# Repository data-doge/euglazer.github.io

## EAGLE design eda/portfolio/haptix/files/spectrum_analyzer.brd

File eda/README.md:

euglazer.github.io
==================

My EDA Phase 0 github pages site

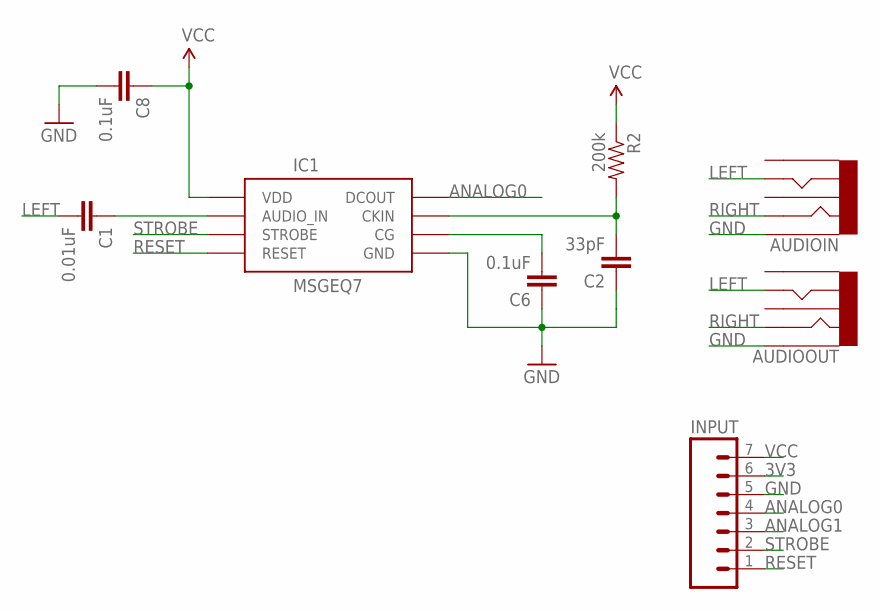
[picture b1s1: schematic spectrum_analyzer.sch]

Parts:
AUDIOIN: AUDIO-JACK2; AUDIO-JACK
AUDIOOUT: AUDIO-JACK2; AUDIO-JACK
C1: 0.01uF; 0603-CAP
C2: 33pF; 0603-CAP
C6, C8: 0.1uF; 0603-CAP
IC1: MSGEQ7DIL; DIL-08
INPUT: M07; 1X07
R2: 200k; 0603-RES

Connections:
3V3: INPUT.6
ANALOG0: IC1.3 (DCOUT), INPUT.4
ANALOG1: INPUT.3
CKIN: C2.2, IC1.8 (CKIN), R2.2
GND: AUDIOIN.1, AUDIOOUT.1, C2.1, C6.1, C8.2, IC1.2 (GND), INPUT.5
LEFT: AUDIOIN.5, AUDIOOUT.5, C1.2
unnamed: C1.1, IC1.5 (AUDIO_IN)
unnamed: C6.2, IC1.6 (CG)
RESET: IC1.7 (RESET), INPUT.1
RIGHT: AUDIOIN.2, AUDIOOUT.2
STROBE: IC1.4 (STROBE), INPUT.2
VCC: C8.1, IC1.1 (VDD), INPUT.7, R2.1

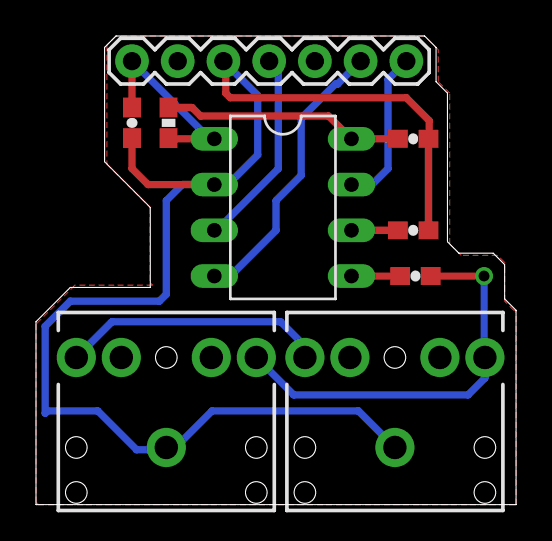
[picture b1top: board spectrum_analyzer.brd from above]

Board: 2 copper layers, 26.7 x 26.0 mm, 9 parts (0 on the bottom side), 10 nets.

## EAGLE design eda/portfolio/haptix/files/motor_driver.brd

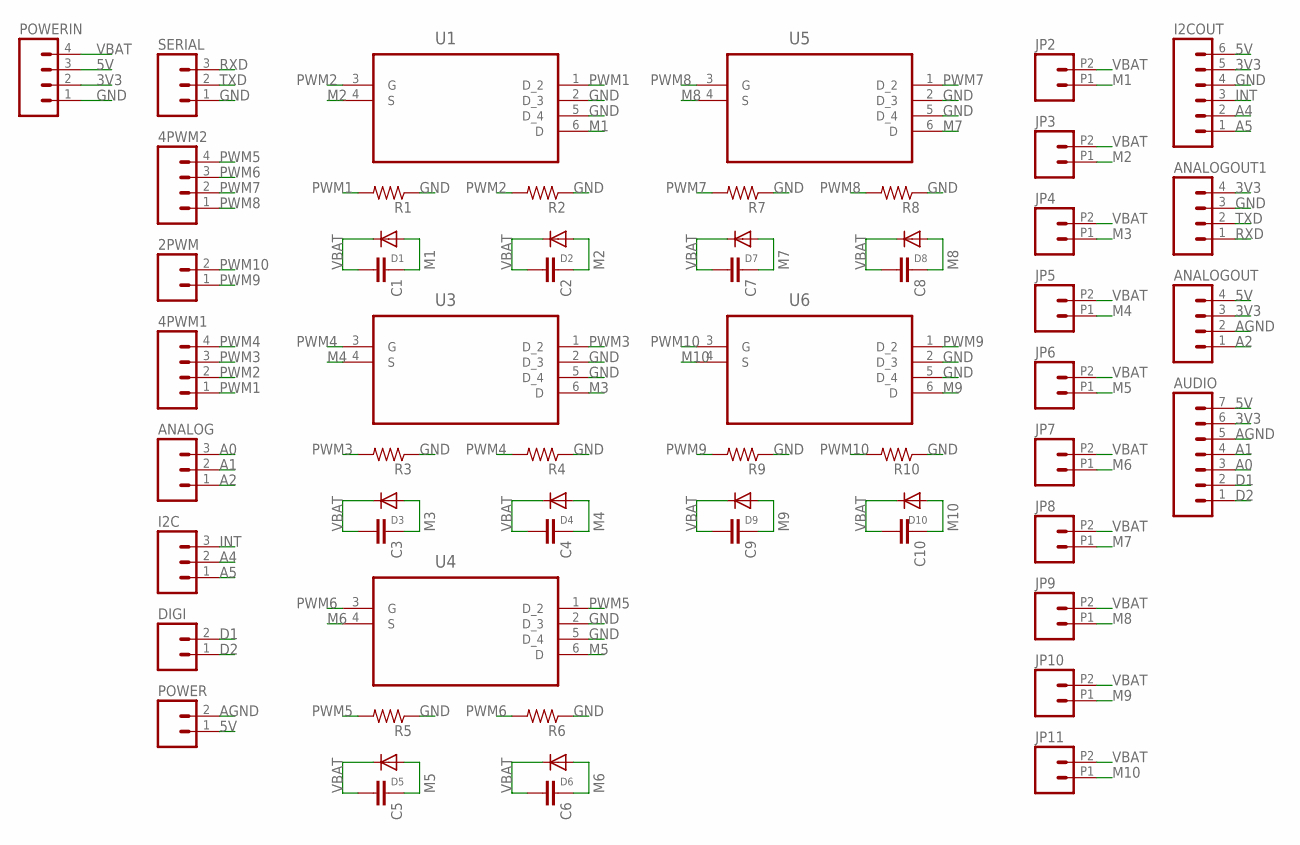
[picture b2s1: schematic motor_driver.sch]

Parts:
2PWM: M02PTH; 1X02
4PWM1, 4PWM2: M04PTH; 1X04
ANALOG: M03PTH; 1X03
ANALOGOUT, ANALOGOUT1: M04PTH; 1X04
AUDIO: M07; 1X07
C1, C2, C3, C4, C5, C6, C7, C8, C9, C10: CAP0603-CAP; 0603-CAP
D1, D2, D3, D4, D5, D6, D7, D8, D9, D10: DIODE_SOD-123FL; SOD-123FL
DIGI: M02PTH; 1X02
I2C: M03PTH; 1X03
I2COUT: M06NO_SILK; 1X06_NO_SILK
JP2, JP3, JP4, JP5, JP6, JP7, JP8, JP9, JP10, JP11: M022.54MM_SCREWTERM; 1X02_2.54_SCREWTERM
POWER: M02PTH; 1X02
POWERIN: M04PTH; 1X04
R1, R2, R3, R4, R5, R6, R7, R8, R9, R10: RESISTOR0603; 0603-RES
SERIAL: M03PTH; 1X03
U1, U3, U4, U5, U6: SI3456DDV-T1-GE3; SOT95P285X110-6N

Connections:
3V3: ANALOGOUT.3, ANALOGOUT1.4, AUDIO.6, I2COUT.5, POWERIN.2
5V: ANALOGOUT.4, AUDIO.7, I2COUT.6, POWER.1, POWERIN.3
A0: ANALOG.3, AUDIO.3
A1: ANALOG.2, AUDIO.4
A2: ANALOG.1, ANALOGOUT.1
A4: I2C.2, I2COUT.2
A5: I2C.1, I2COUT.1
AGND: ANALOGOUT.2, AUDIO.5, POWER.2
D1: AUDIO.2, DIGI.2
D2: AUDIO.1, DIGI.1
GND: ANALOGOUT1.3, I2COUT.4, POWERIN.1, R1.1, R2.1, R3.1, R4.1, R5.1, R6.1, R7.1, R8.1, R9.1, R10.1, SERIAL.1, U1.2 (D_3), U1.5 (D_4), U3.2 (D_3), U3.5 (D_4), U4.2 (D_3), U4.5 (D_4), U5.2 (D_3), U5.5 (D_4), U6.2 (D_3), U6.5 (D_4)
INT: I2C.3, I2COUT.3
M1: C1.1, D1.A, JP2.P1 (1), U1.6 (D)
M2: C2.1, D2.A, JP3.P1 (1), U1.4 (S)
M3: C3.1, D3.A, JP4.P1 (1), U3.6 (D)
M4: C4.1, D4.A, JP5.P1 (1), U3.4 (S)
M5: C5.1, D5.A, JP6.P1 (1), U4.6 (D)
M6: C6.1, D6.A, JP7.P1 (1), U4.4 (S)
M7: C7.1, D7.A, JP8.P1 (1), U5.6 (D)
M8: C8.1, D8.A, JP9.P1 (1), U5.4 (S)
M9: C9.1, D9.A, JP10.P1 (1), U6.6 (D)
M10: C10.1, D10.A, JP11.P1 (1), U6.4 (S)
PWM1: 4PWM1.1, R1.2, U1.1 (D_2)
PWM2: 4PWM1.2, R2.2, U1.3 (G)
PWM3: 4PWM1.3, R3.2, U3.1 (D_2)
PWM4: 4PWM1.4, R4.2, U3.3 (G)
PWM5: 4PWM2.4, R5.2, U4.1 (D_2)
PWM6: 4PWM2.3, R6.2, U4.3 (G)
PWM7: 4PWM2.2, R7.2, U5.1 (D_2)
PWM8: 4PWM2.1, R8.2, U5.3 (G)
PWM9: 2PWM.1, R9.2, U6.1 (D_2)
PWM10: 2PWM.2, R10.2, U6.3 (G)
RXD: ANALOGOUT1.1, SERIAL.3
TXD: ANALOGOUT1.2, SERIAL.2
VBAT: C1.2, C2.2, C3.2, C4.2, C5.2, C6.2, C7.2, C8.2, C9.2, C10.2, D1.C, D2.C, D3.C, D4.C, D5.C, D6.C, D7.C, D8.C, D9.C, D10.C, JP2.P2 (2), JP3.P2 (2), JP4.P2 (2), JP5.P2 (2), JP6.P2 (2), JP7.P2 (2), JP8.P2 (2), JP9.P2 (2), JP10.P2 (2), JP11.P2 (2), POWERIN.4

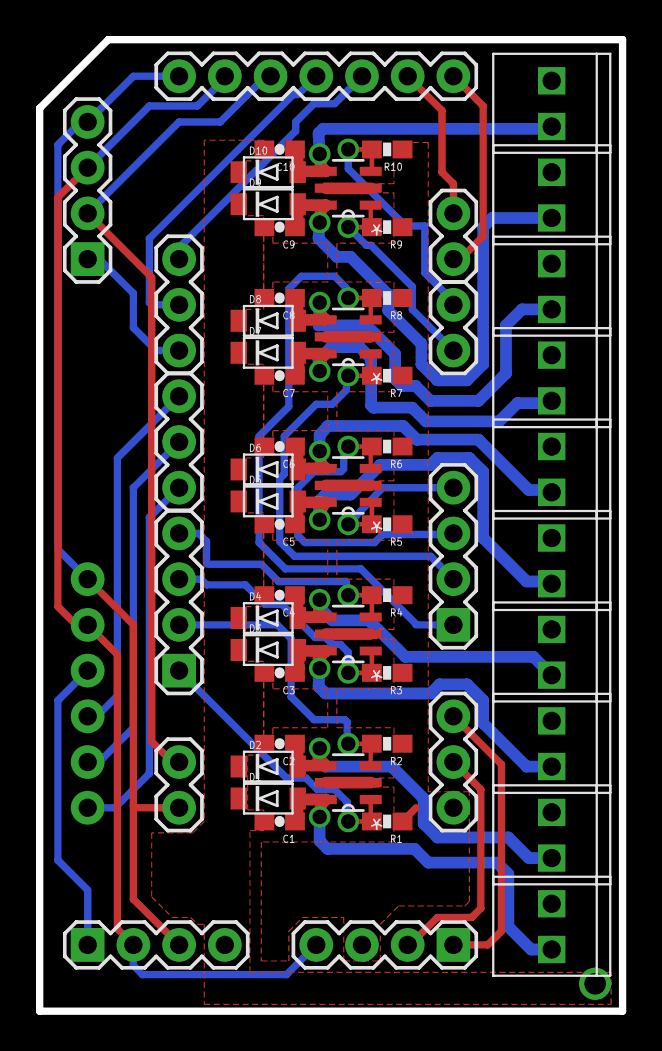
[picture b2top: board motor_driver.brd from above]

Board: 2 copper layers, 32.4 x 54.0 mm, 58 parts (0 on the bottom side), 35 nets.

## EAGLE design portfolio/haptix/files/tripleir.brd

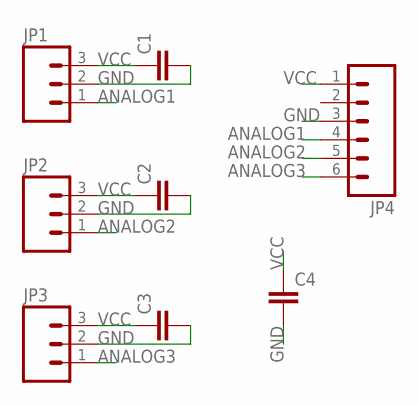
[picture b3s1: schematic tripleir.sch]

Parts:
C1, C2, C3, C4: CAP0603-CAP; 0603-CAP
JP1, JP2, JP3: M03LONGPADS; 1X03_LONGPADS
JP4: M06SIP; 1X06

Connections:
ANALOG1: JP1.1, JP4.4
ANALOG2: JP2.1, JP4.5
ANALOG3: JP3.1, JP4.6
GND: C1.2, C2.2, C3.2, C4.2, JP1.2, JP2.2, JP3.2, JP4.3
VCC: C1.1, C2.1, C3.1, C4.1, JP1.3, JP2.3, JP3.3, JP4.1

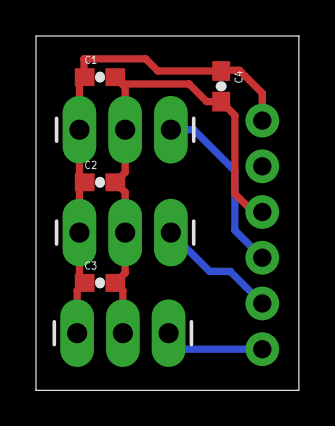
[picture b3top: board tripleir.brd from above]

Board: 2 copper layers, 14.6 x 19.7 mm, 8 parts (0 on the bottom side), 5 nets.

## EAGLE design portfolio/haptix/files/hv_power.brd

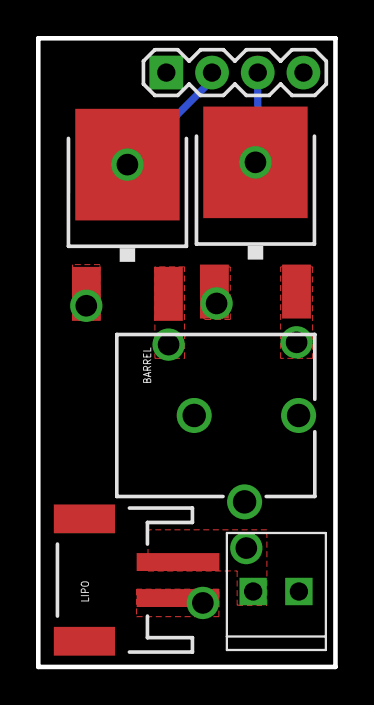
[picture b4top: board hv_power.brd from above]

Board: 2 copper layers, 16.5 x 34.9 mm, 6 parts (0 on the bottom side), 4 nets.

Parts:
3V3REG, 5VREG: V_REG_317DPACK; V-REG_DPACK
BARREL: POWER_JACKPTH_BREAD; POWER_JACK_PTH_BREAD
LIPO: JST-2-SMD
OUT: 1X04
SCREW: M022.54MM_SCREWTERM; 1X02_2.54_SCREWTERM

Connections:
3V3: 3V3REG.4, OUT.2
5V: 5VREG.4, OUT.3
GND: 3V3REG.1, 5VREG.1, BARREL.GND, LIPO.1, OUT.1, SCREW.P2
VBAT: 3V3REG.3, 5VREG.3, BARREL.PWR, LIPO.2, OUT.4, SCREW.P1

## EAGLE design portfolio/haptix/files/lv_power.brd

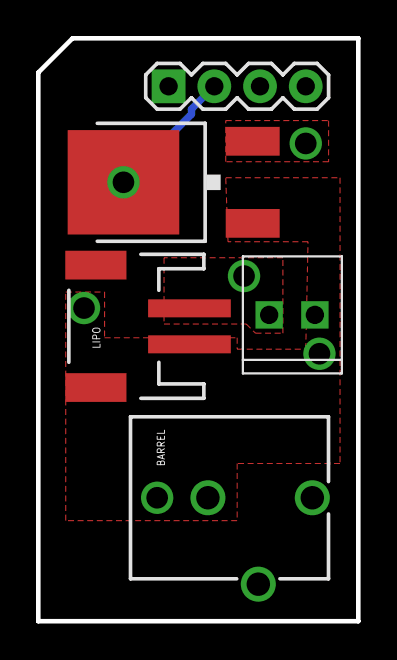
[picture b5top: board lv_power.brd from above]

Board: 2 copper layers, 17.8 x 32.4 mm, 5 parts (0 on the bottom side), 3 nets.

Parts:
3V3REG: V_REG_317DPACK; V-REG_DPACK
BARREL: POWER_JACKPTH_BREAD; POWER_JACK_PTH_BREAD
LIPO: M02-JST-2MM-SMT; JST-2-SMD
OUT: 1X04
SCREW: M022.54MM_SCREWTERM; 1X02_2.54_SCREWTERM

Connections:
3V3: 3V3REG.4, OUT.2
GND: 3V3REG.1, BARREL.GND, LIPO.1, OUT.1, SCREW.P2
VBAT: 3V3REG.3, BARREL.PWR, LIPO.2, OUT.3, OUT.4, SCREW.P1

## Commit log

2014-09-21 Added index page
2014-09-22 added new unit1_projects folder, with a stylesheets and images folder, and uploaded files for first basic website
2014-09-22 deleted duplicate file
2014-09-23 added blog-posts folder containing images + stylesheets folders, and a first html/css mockup for a blog template
2014-09-24 renamed blog template
2014-09-24 updated blog_tempates: changed header sizes; created week1_technical blog post from template
2014-09-24 updated index.html with directory pointing to all the sites i've made so far
2014-09-24 modifed blog template: links now underlined; added new week1_cultural blog post
2014-09-24 revised blog template: removed .link class, changed sidebar links to <a> links which refer to my other blog posts, changed about button to a link which refers to my personal page
2014-09-24 Replace master branch with page content via GitHub
2014-09-24 deleted submodule shit
2014-09-24 moved index.html to root
2014-09-24 updated index.html with proper links
2014-09-25 fixed links in index
2014-09-25 revised and styled index: added stylesheets and images folder to root; deleted files from prior unsuccessful attempt at getting githubpages to work
2014-09-25 added heart to index
2014-09-25 created wireframe website: added images and stylesheet to appropriate folders
2014-09-25 revised index: added link to wireframing site
2014-09-26 added 2.2 practice files
2014-09-26 Revised index.html: changed to semantic html, and added attributes to make more responsive; also, started creating portfolio website based off of index
2014-09-26 revised index so that image in about floats left.; also, created my_wireframe.html
2014-09-26 added my_wireframe.html: added images and a new stylesheet; revised wireframe_sites html/css: added reset.css, employed semantic html, made more responsive
2014-09-26 revised index, added my_wireframe to projects list
2014-09-26 index: lowercase i
2014-09-27 revised blog template: have external reset.css file, semantic html, responsive design, fixed links; also, created week2_technical.html from new template
2014-09-27 added week2_tech blog post
2014-09-27 updated index.html with week2tech blog post
2014-09-27 added date to title
2014-09-28 added link for about button
2014-09-28 updated project titles on index
2014-09-28 deleted first paragraph -- unncessary
2014-09-30 added w3 cultural blog post, updated all other blog posts with links, updated portfolio
2014-10-06 updated portfolio content, pictures, etc.
2014-10-13 updated a:hover on blog template
2014-10-13 added week3 technical blog, and updated blog template and all other blogs with full listing of posts
2014-10-13 added week4 tech blog post; changed index to point to all blog posts; changes to my portfolio
2014-10-15 added haptix node portfolio shit
2014-10-15 formatted pictures
2014-10-15 capitalization
2014-11-01 finished haptix node page, reformatted index page, reformatted projects_template.html
2014-11-01 finished chemical laptop shit, minor changes to footer in project_template
2014-11-01 began intros for laser harps and pisces
2014-11-02 added introduction and pictures to pisces, slightly rewrote index page{
2014-11-02 capitalization of jpg
2014-11-02 added pictures for irwhitecane and audiotactile backpack and some basic info
2014-11-29 added figure captions to PISCES
2014-12-21 reorganized folders into EDA, added new pages site
2014-12-21 grammar lol
2014-12-21 target blank to links
2015-02-16 add html
2015-02-16 add css
2015-02-16 add index.js
2015-02-16 add waves.js
2015-02-18 add id seed
2015-04-24 update picture
2015-04-24 add fuckafucka
2015-10-06 start of website
2015-10-06 add materials and setup
2015-10-06 add xiaohan.jpg; short description of xiaohan
2015-10-06 add eugene picture
2015-10-06 style header
2015-10-06 description of videos
2015-10-06 add + style images of materials
2015-10-06 things lol
2015-10-06 update skillset
2015-10-06 make header text more visible
2015-10-06 add diagram
2015-10-06 change title
2015-10-06 rename project

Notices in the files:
parts and their libraries:
SparkFun-Capacitors: Licensing: Creative Commons ShareAlike 4.0 International - https://creativecommons.org/licenses/by-sa/4.0
